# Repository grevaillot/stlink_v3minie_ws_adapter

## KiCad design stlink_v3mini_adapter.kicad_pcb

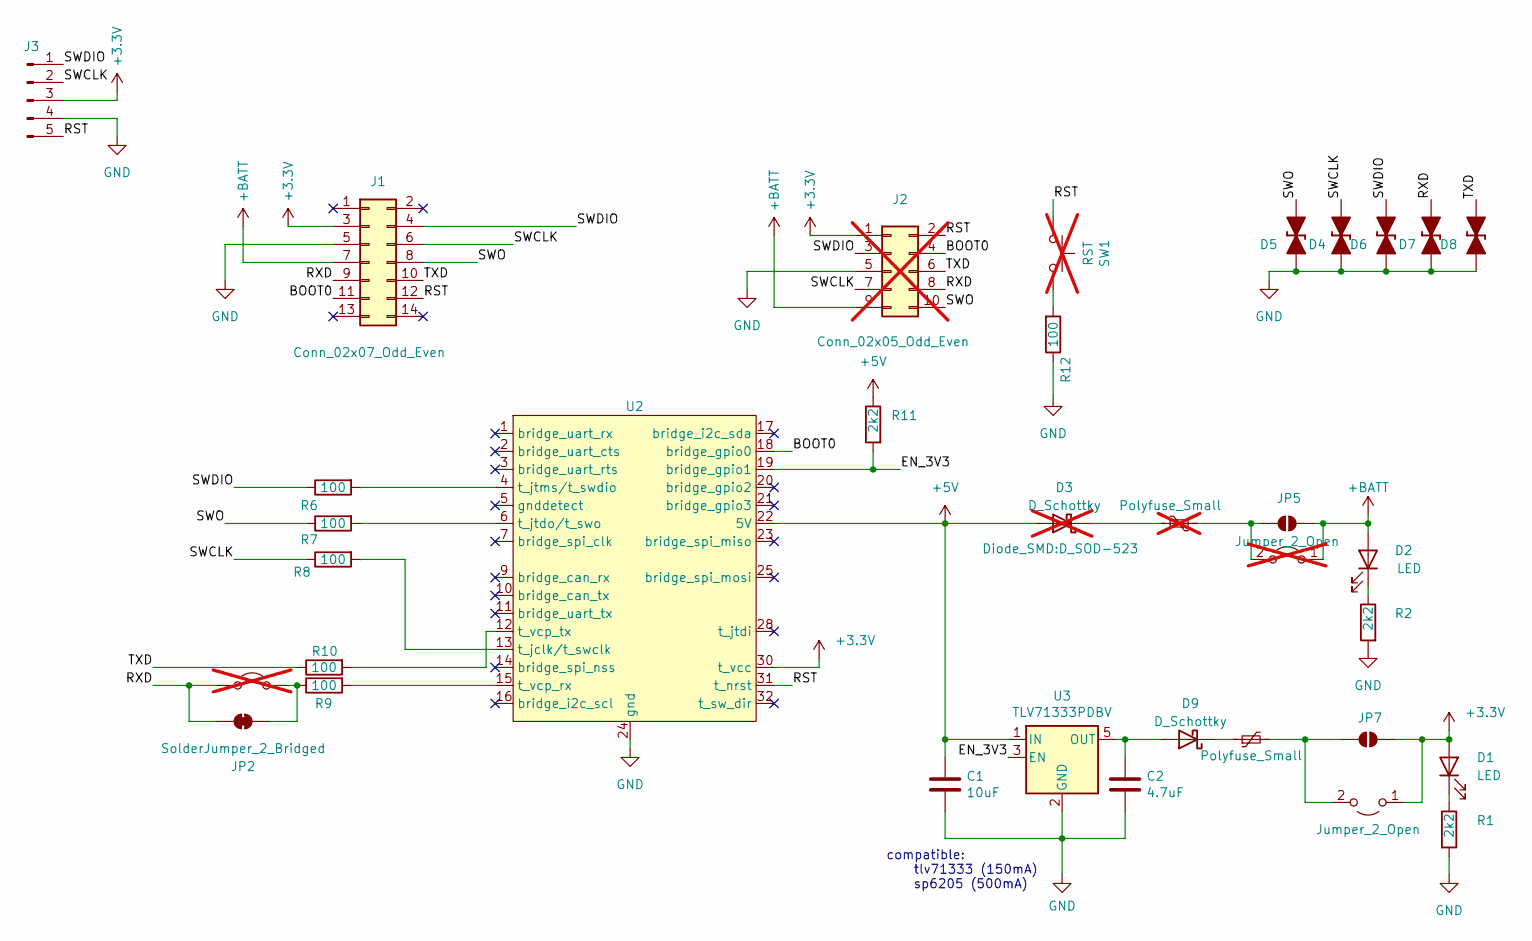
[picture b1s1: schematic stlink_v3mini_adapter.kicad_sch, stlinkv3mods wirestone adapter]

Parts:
C1: 10uF; C_0805_2012Metric
C2: 4.7uF; C_0805_2012Metric
D1, D2: LED; LED_0603_1608Metric
D3: D_Schottky; D_SOD-523; not fitted
D4, D5, D6, D7, D8: PESD3V3L1BA; R_0603_1608Metric
D9: D_Schottky; D_SOD-523
F2: Polyfuse_Small; Fuse_0603_1608Metric
F3: Polyfuse_Small; Fuse_0603_1608Metric; not fitted
J1: Conn_02x07_Odd_Even; PinHeader_2x07_P1.27mm_Vertical_SMD; LCSC C6332251
J2: Conn_02x05_Odd_Even; PinHeader_2x05_P2.54mm_Vertical_SMD; not fitted
J3: Conn_01x05_Pin; PinHeader_1x05_P2.54mm_Vertical
JP1, JP3: Jumper_2_Open; PinSocket_1x02_P2.54mm_Vertical; not fitted
JP2: SolderJumper_2_Bridged; SolderJumper-2_P1.3mm_Bridged_RoundedPad1.0x1.5mm
JP4: Jumper_2_Open; PinSocket_1x02_P2.54mm_Vertical
JP5, JP7: SolderJumper_2_Bridged; SolderJumper-2_P1.3mm_Open_RoundedPad1.0x1.5mm
R1, R2, R11: 2k2; R_0402_1005Metric
R6, R7, R8, R9, R10, R12: 100; R_0402_1005Metric
SW1: RST; SW_Push_1P1T_NO_6x6mm_H9.5mm; JLCPCB C221880; not fitted
U2: STLINK-V3MODS
U3: TLV71333PDBV; SOT-23-5

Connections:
+3.3V: D1.2 (A), J1.3, J2.1, J3.3, JP4.1 (A), JP7.2 (B), U2.30 (t_vcc)
+5V: C1.1, D3.2 (A), R11.1, U2.22 (5V), U3.1 (IN)
+BATT: D2.2 (A), J1.7, J2.9, JP3.1 (A), JP5.2 (B)
/BOOT0: J1.11, J2.4, U2.18 (bridge_gpio0)
/EN_3V3: R11.2, U2.19 (bridge_gpio1), U3.3 (EN)
/RST: J1.12, J2.2, J3.5, SW1.1, U2.31 (t_nrst)
/RXD: D7.1 (K), J1.9, J2.8, JP1.2 (B), JP2.2 (B)
/SWCLK: D4.1 (K), J1.6, J2.7, J3.2, R8.1
/SWDIO: D6.1 (K), J1.4, J2.3, J3.1, R6.1
/SWO: D5.1 (K), J1.8, J2.10, R7.1
/TXD: D8.1 (K), J1.10, J2.6, R10.1
GND: C1.2, C2.2, D4.2 (A), D5.2 (A), D6.2 (A), D7.2 (A), D8.2 (A), J1.5, J2.5, J3.4, R1.2, R2.2, R12.1, U2.8 (gnd), U2.24 (gnd), U2.26 (gnd), U2.27 (gnd), U2.29 (gnd), U3.2 (GND)
unnamed: D1.1 (K), R1.1
unnamed: D2.1 (K), R2.1
unnamed: D3.1 (K), F3.2
unnamed: C2.1, D9.2 (A), U3.5 (OUT)
unnamed: D9.1 (K), F2.1
unnamed: JP1.1 (A), JP2.1 (A), R9.1
unnamed: F3.1, JP3.2 (B), JP5.1 (A)
unnamed: F2.2, JP4.2 (B), JP7.1 (A)
unnamed: R12.2, SW1.2
unnamed: R8.2, U2.13 (t_jclk/t_swclk)
unnamed: R7.2, U2.6 (t_jtdo/t_swo)
unnamed: R6.2, U2.4 (t_jtms/t_swdio)
unnamed: R9.2, U2.15 (t_vcp_rx)
unnamed: R10.2, U2.12 (t_vcp_tx)

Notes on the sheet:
compatible: tlv71333 (150mA) sp6205 (500mA)

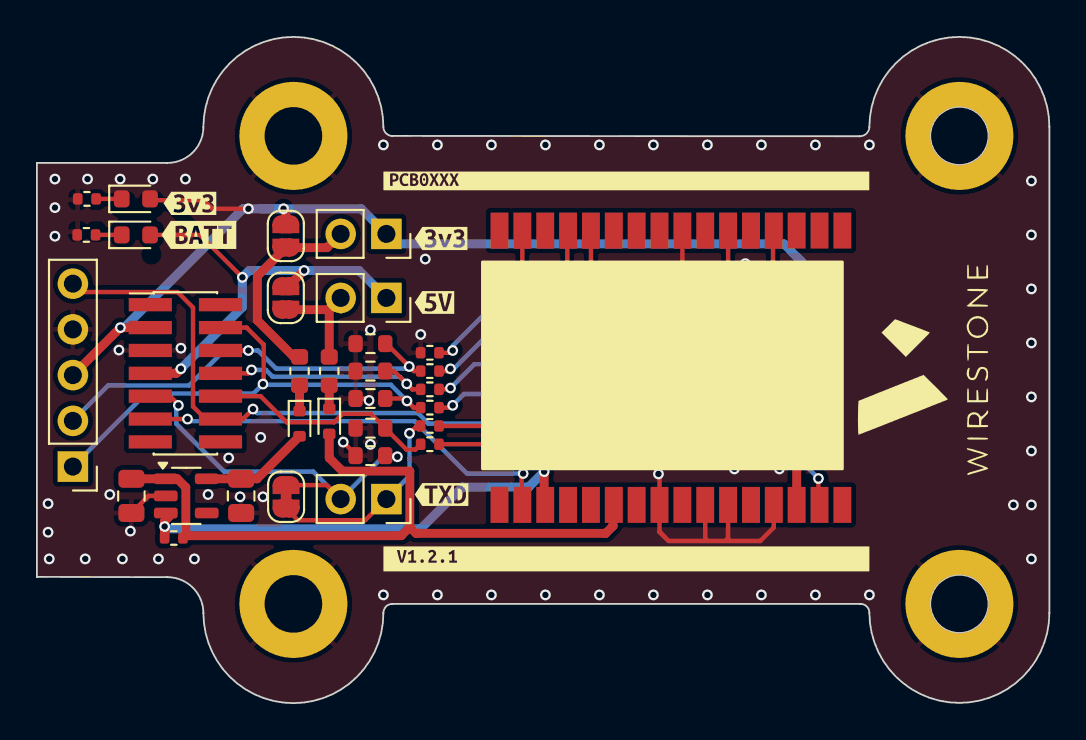
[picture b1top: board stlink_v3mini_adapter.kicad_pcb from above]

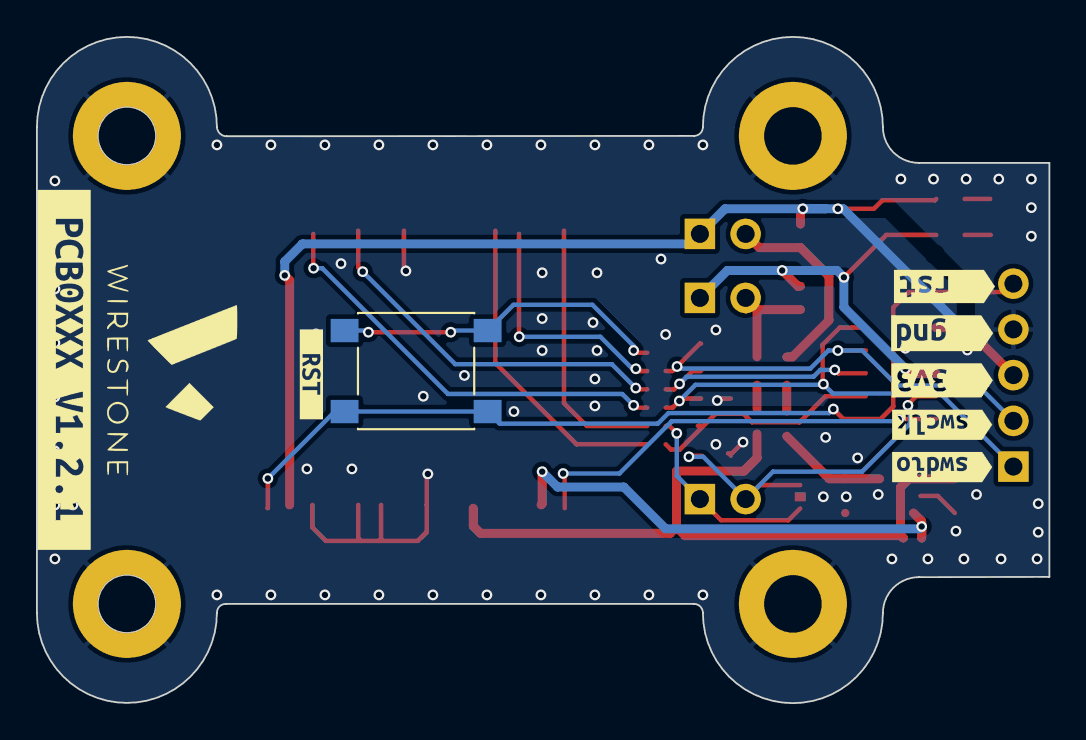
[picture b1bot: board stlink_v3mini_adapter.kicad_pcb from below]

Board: 2 copper layers, 56.2 x 37.0 mm, 47 parts (8 on the bottom side), 26 nets.

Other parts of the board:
kibuzzard-63CA65D0: G***; kibuzzard-63CA65D0
kibuzzard-63D24B36: G***; kibuzzard-63D24B36
kibuzzard-63D24BD9, kibuzzard-63D24BD9#2: G***; kibuzzard-63D24BD9
kibuzzard-66EBEE9F: G***; kibuzzard-66EBEE9F
kibuzzard-649958AB: G***; kibuzzard-649958AB
kibuzzard-649958B3: G***; kibuzzard-649958B3
kibuzzard-672391A6: G***; kibuzzard-672391A6
kibuzzard-672391AE: G***; kibuzzard-672391AE
kibuzzard-674495BA: G***; kibuzzard-674495BA
kibuzzard-67239188: G***; kibuzzard-67239188
kibuzzard-67239190: G***; kibuzzard-67239190
kibuzzard-67239196: G***; kibuzzard-67239196
kibuzzard-67449540: G***; kibuzzard-67449540

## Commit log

2023-01-24 plop
2023-01-25 add screws, switch to 2 layers
2023-06-26 1.1.0 with tx jumper
2024-10-30 regen exports
2024-10-30 cleanup
2024-10-31 v1.2.0: add simple connector
2024-11-26 1.2.1: actually cut RX instead of TX..
2025-05-05 swap leds for 5v/3v3
2025-05-05 regen
